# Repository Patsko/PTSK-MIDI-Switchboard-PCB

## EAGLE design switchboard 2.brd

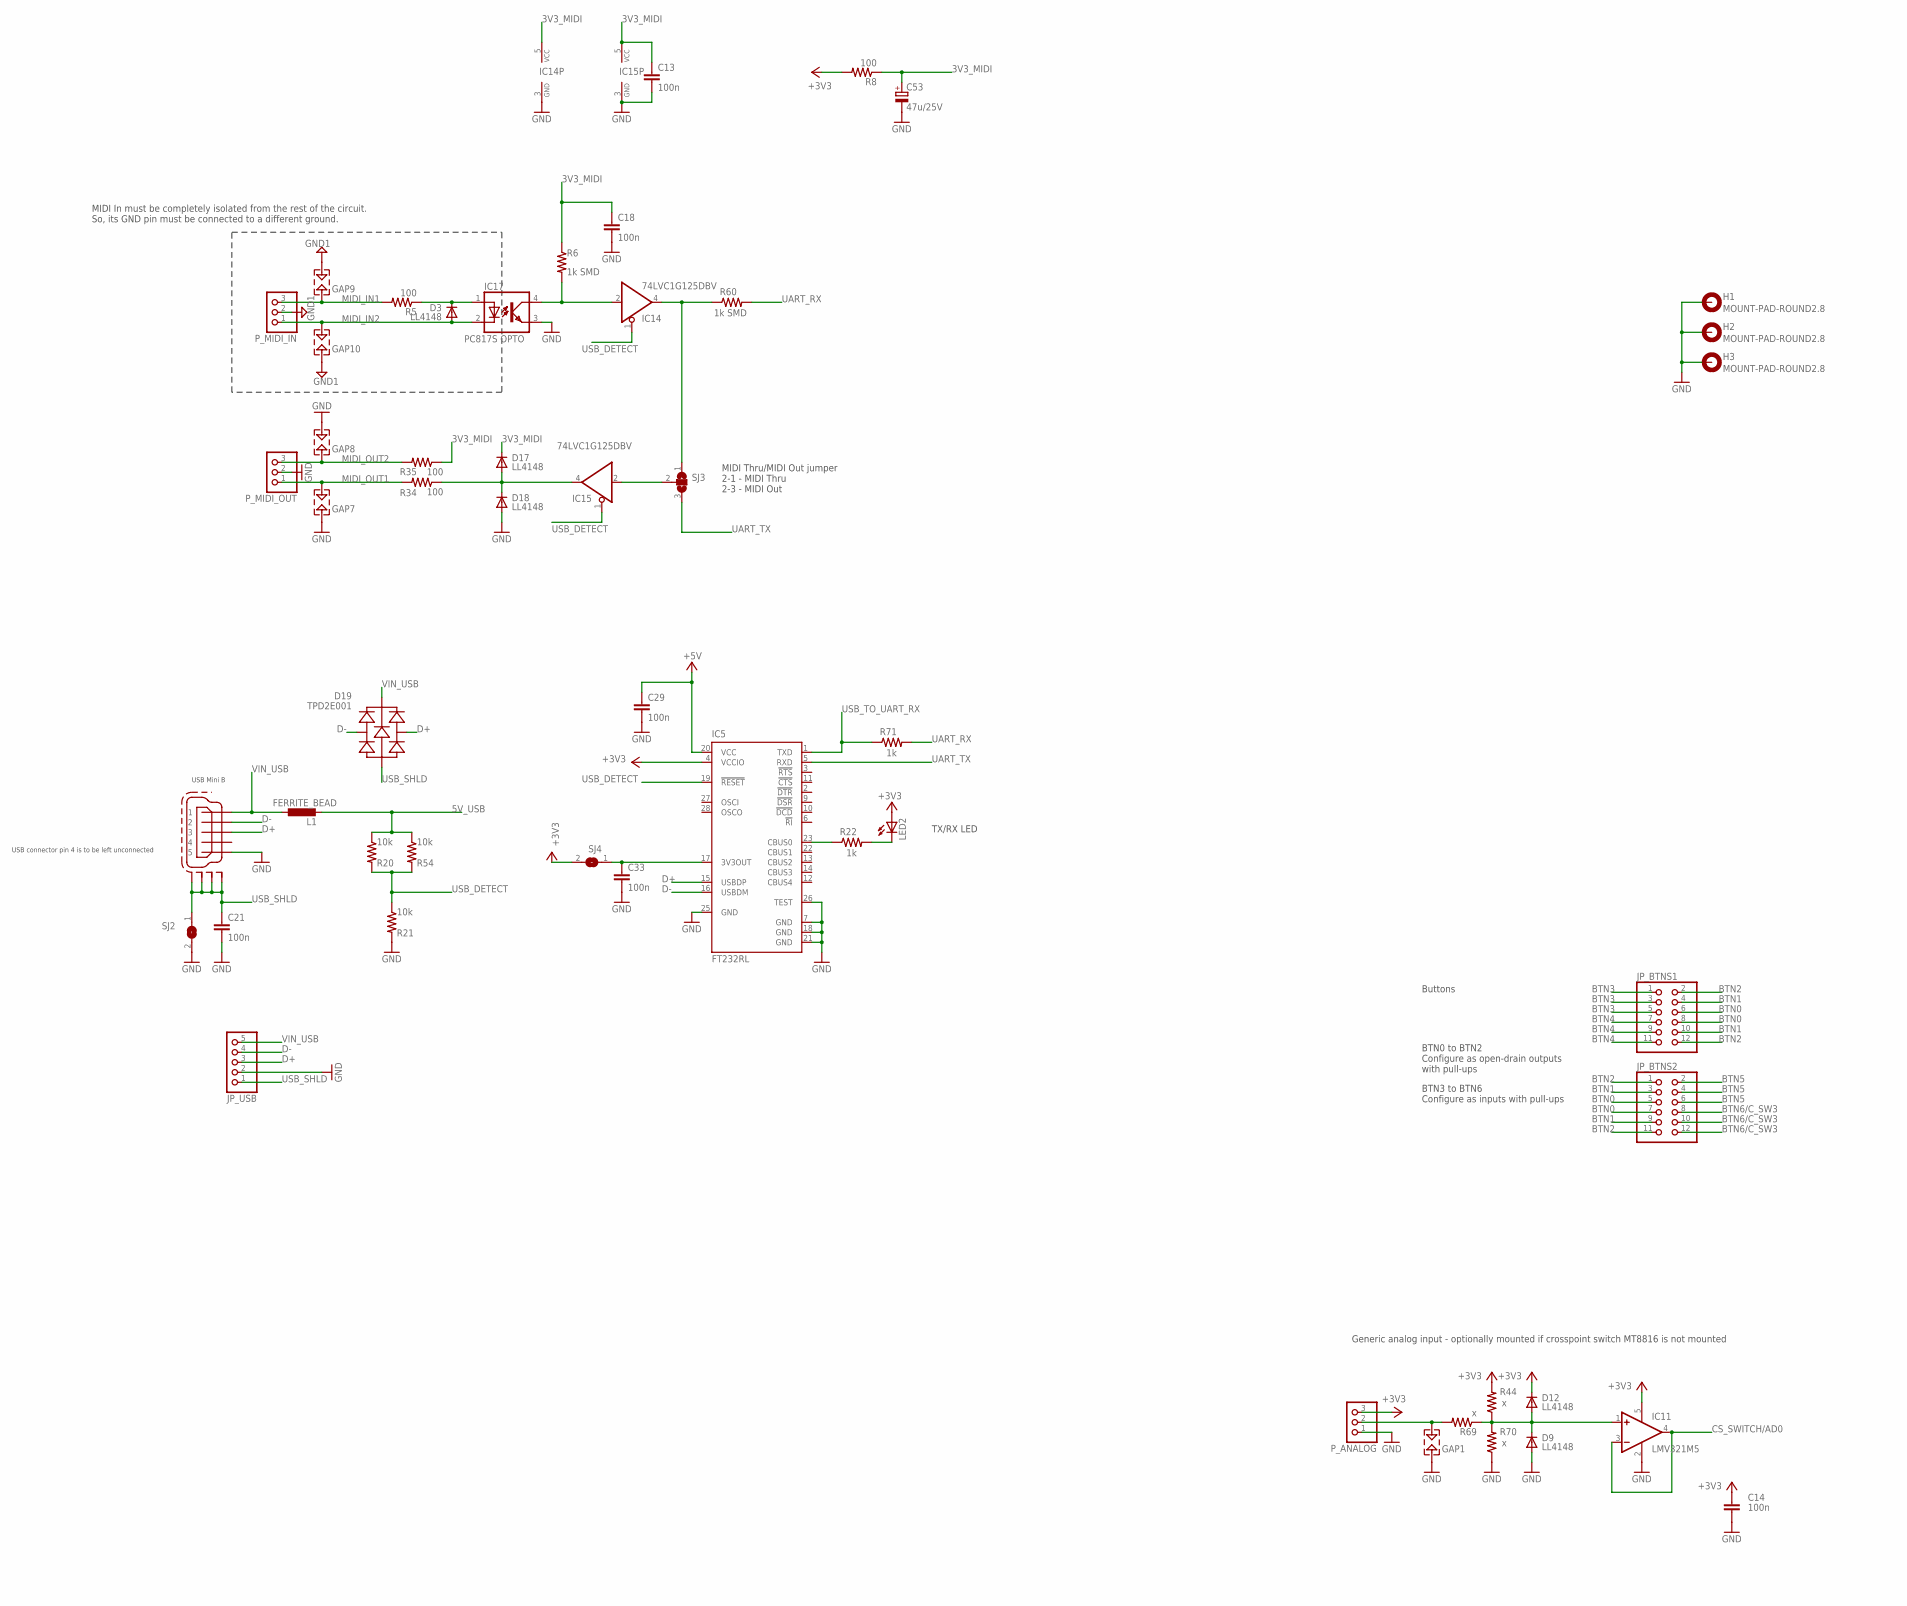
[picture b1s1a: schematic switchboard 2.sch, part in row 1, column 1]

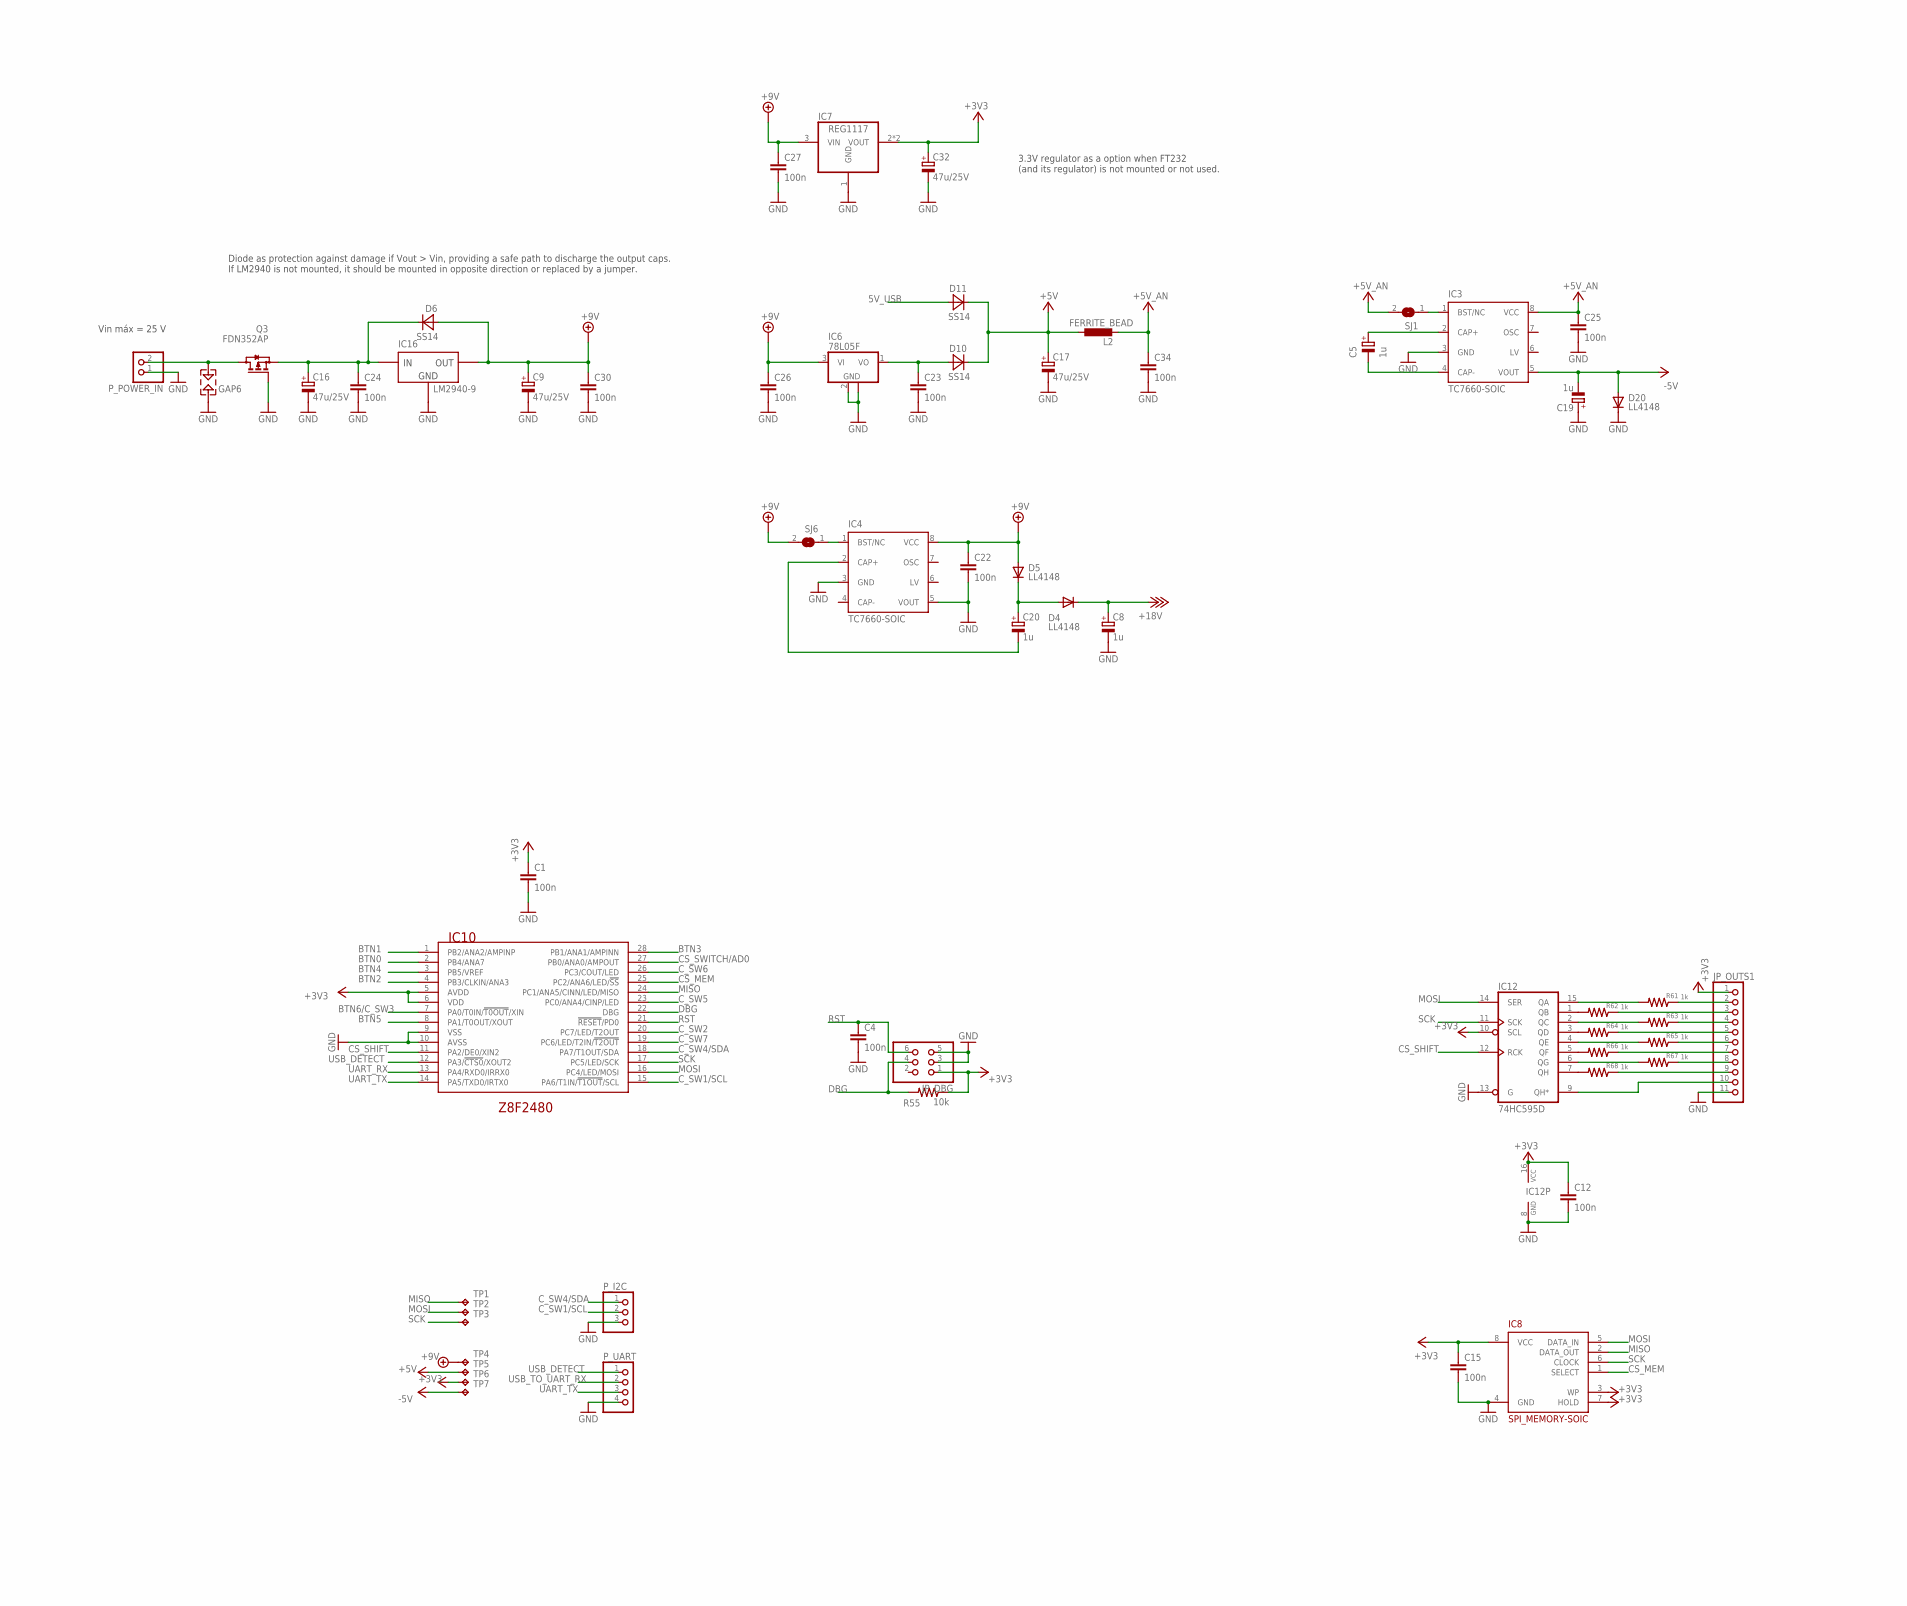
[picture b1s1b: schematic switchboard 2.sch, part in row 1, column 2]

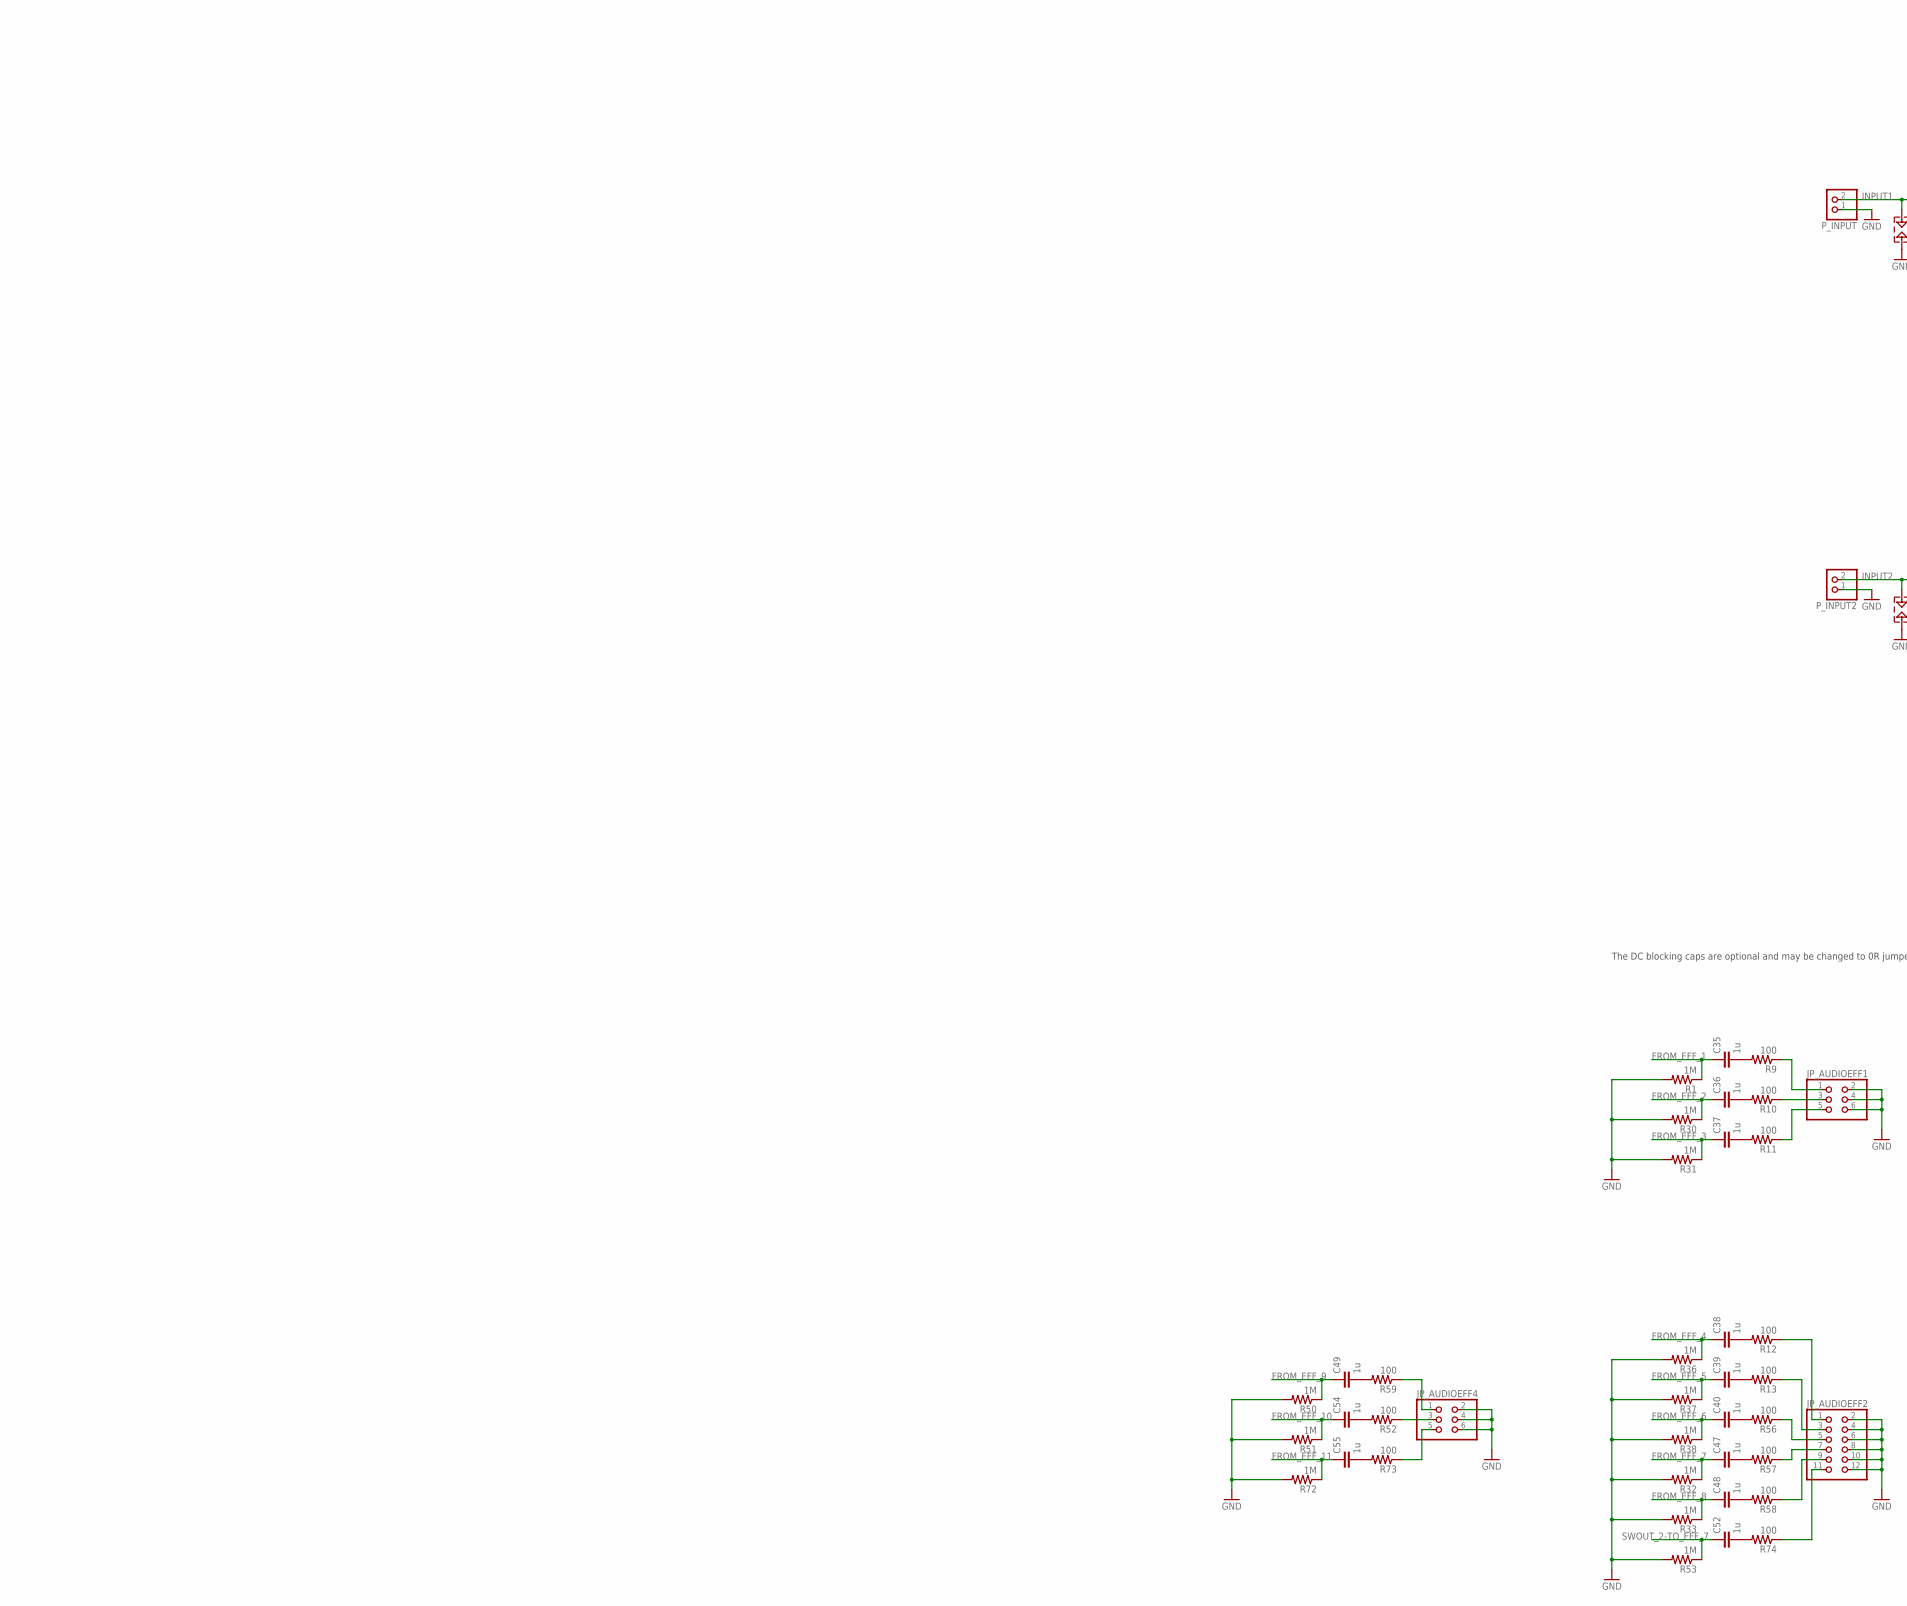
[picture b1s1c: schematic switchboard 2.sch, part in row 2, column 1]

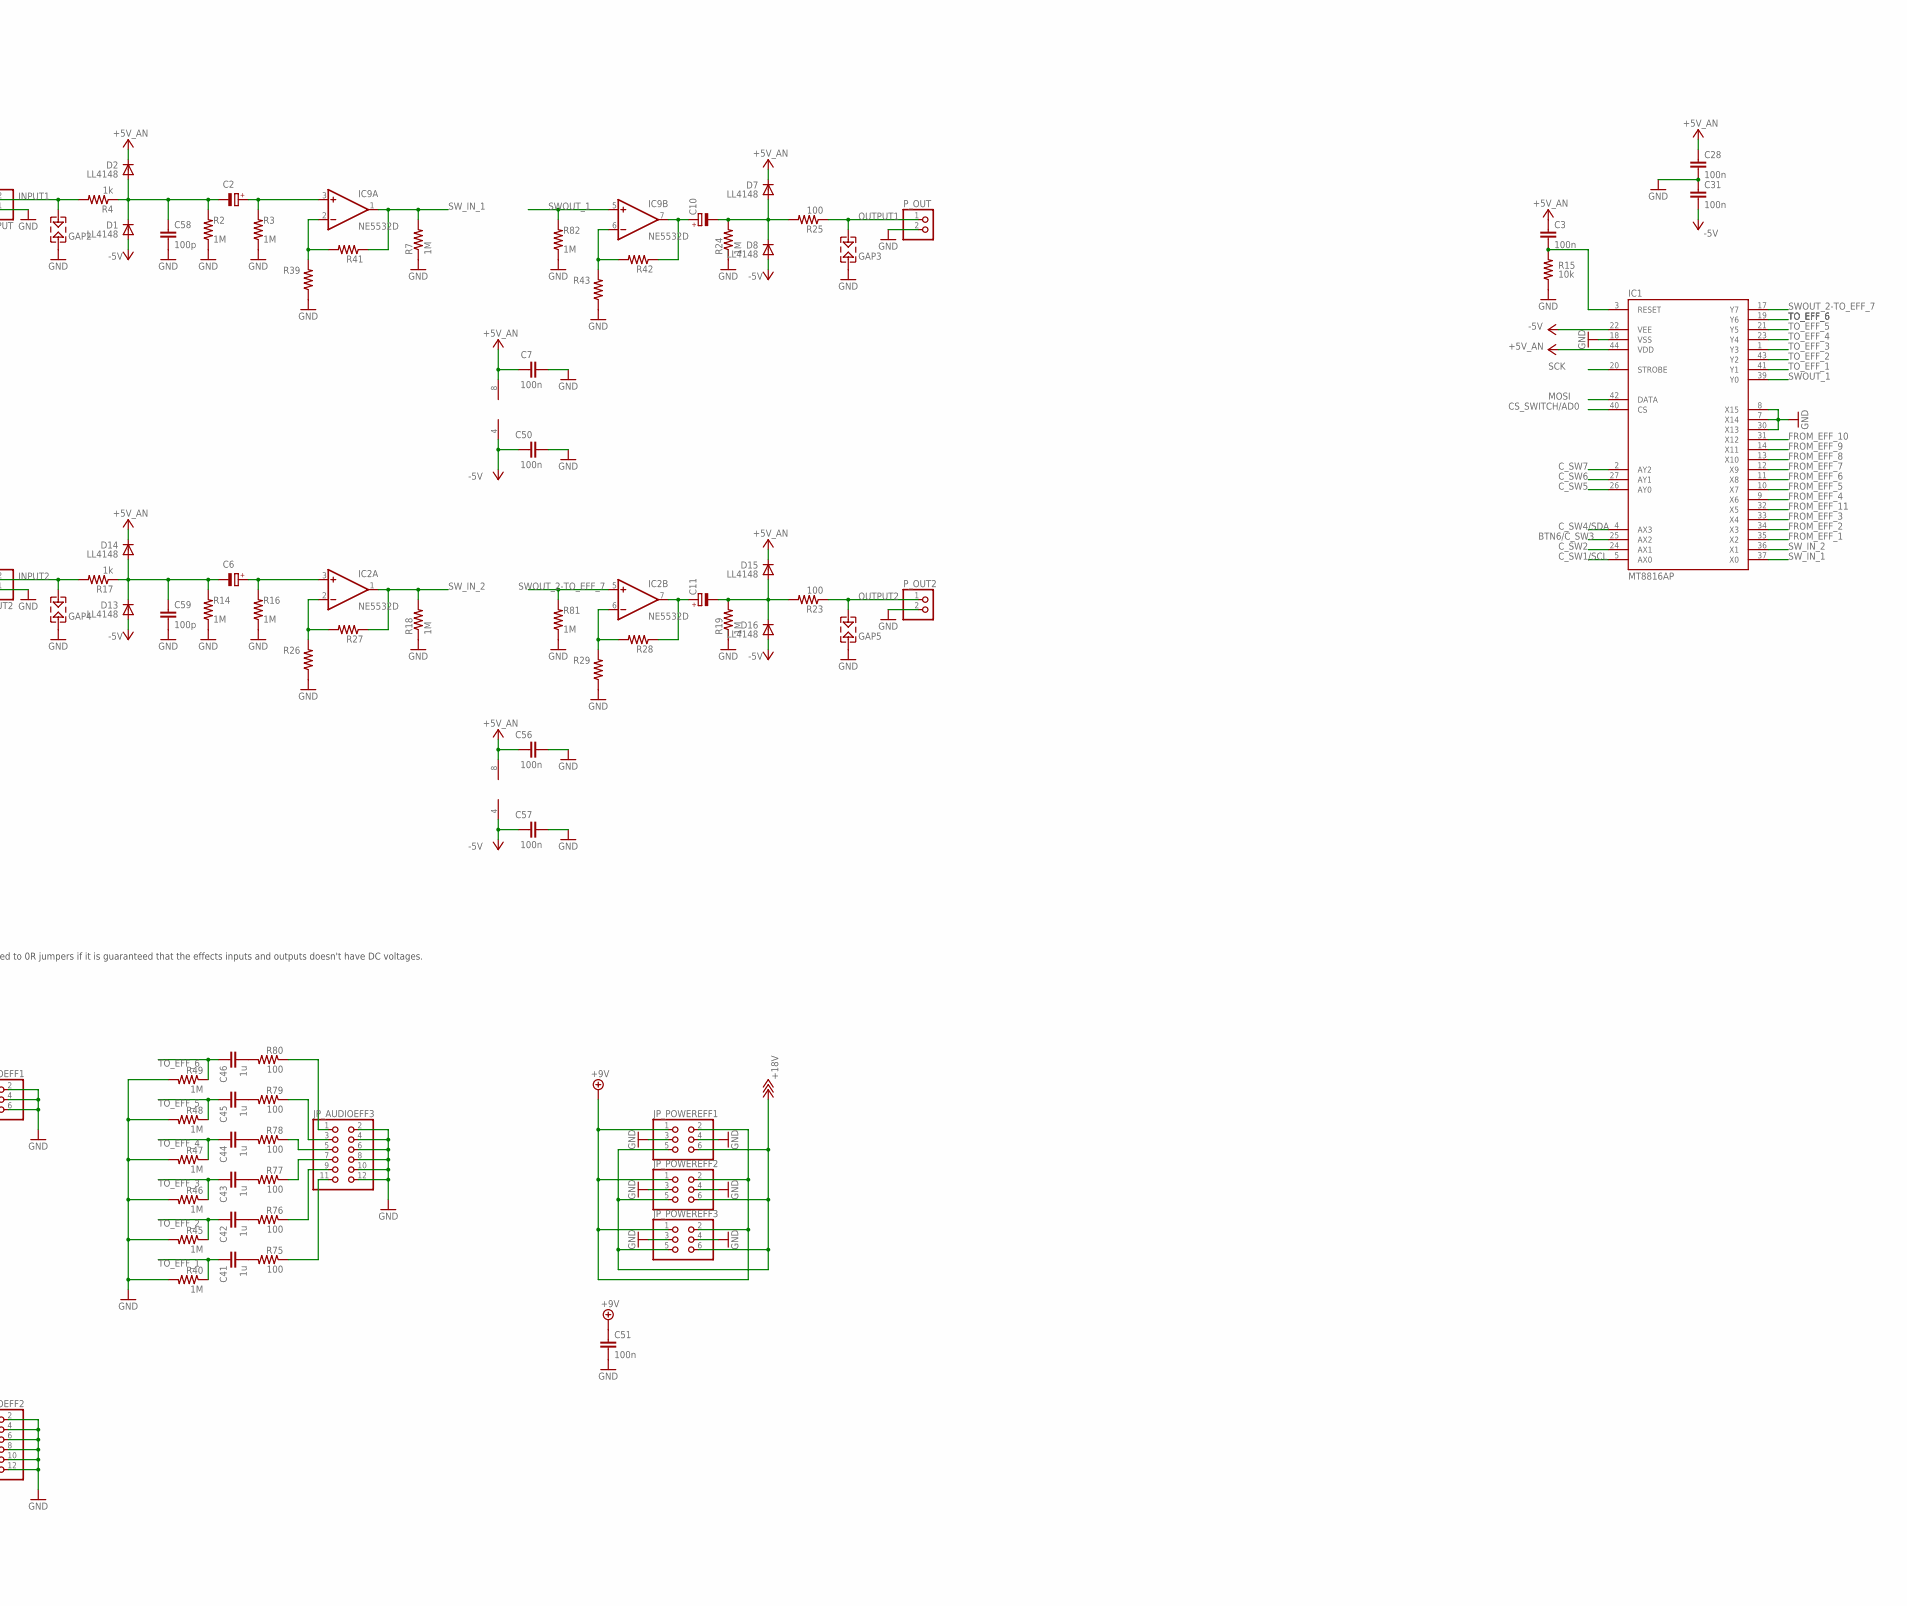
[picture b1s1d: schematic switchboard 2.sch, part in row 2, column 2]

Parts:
C1, C3, C4, C7, C12, C13, C14, C15, C18, C26, C28, C29, C30, C31, C33, C50, C51, C56, C57: 100n; C0603
C2, C6, C10, C11: CAP_POL; SMB-SMA-0805-0603
C5, C8, C19, C20: 1u; SMB-SMA-0805-0603
C9, C16, C17, C32, C53: 47u/25V; ALUMINUM-TANTALUM-CAP
C21, C22, C23, C24, C25, C27, C34: 100n; C0805
C35, C36, C37, C38, C39, C40, C41, C42, C43, C44, C45, C46, C47, C48, C49, C52, C54, C55: 1u; C0603
C58, C59: 100p; C0603
D1, D2, D3, D4, D5, D7, D8, D9, D12, D13, D14, D15, D16, D17, D18, D20: LL4148; MINIMELF
D6, D10, D11: SS14; SMA
D19: TPD2E001; SOT143B
GAP1, GAP2, GAP3, GAP4, GAP5, GAP6, GAP7, GAP8, GAP9, GAP10: SPARK_GAP; SPARK-GAP-8
H1, H2, H3: MOUNT-PAD-ROUND2.8; 2,8-PAD
IC1: MT8816AP; PLCC44
IC2, IC9: NE5532D; SO08
IC3, IC4: TC7660-SOIC; SOIC08
IC5: FT232RL; SSOP28
IC6: 78L05F; SOT89
IC7: REG1117; SOT223
IC8: SPI_MEMORY-SOIC; SOIC08
IC10: Z8F2480SO; SO28W
IC11: LMV321M5; SOT23-5
IC12: 74HC595D; SO16
IC14, IC15: 74LVC1G125DBV; SOT23-5
IC16: LM2940-9; SOT223
IC17: PC817S OPTO; DIL4-SMD
JP_AUDIOEFF1, JP_AUDIOEFF4: PINHD-2X03_2.54-SMD; 2X03SMD
JP_AUDIOEFF2, JP_AUDIOEFF3: PINHD-2X06_2.54-SMD; 2X06SMD
JP_BTNS1, JP_BTNS2: PINHD-2X06_2.54-SMD; 2X06SMD
JP_DBG: PINHD-2X3; 2X03
JP_OUTS1: PINHD-1X11; 1X11
JP_POWEREFF1, JP_POWEREFF2, JP_POWEREFF3: PINHD-2X03_2.54-SMD; 2X03SMD
JP_USB: PINHD-1X5; 1X05
L1, L2: FERRITE_BEAD; 0805
LED2: LEDCHIPLED_0805; CHIPLED_0805
P_ANALOG: PINHD-1X3; 1X03
P_I2C: PINHD-1X3; 1X03
P_INPUT, P_INPUT2: PINHD-1X2; 1X02
P_MIDI_IN: PINHD-1X3; 1X03
P_MIDI_OUT: PINHD-1X3; 1X03
P_OUT, P_OUT2: PINHD-1X2; 1X02
P_POWER_IN: PINHD-1X2; 1X02
P_UART: PINHD-1X4; 1X04
Q3: FDN352AP; SOT23
R1, R2, R3, R7, R14, R16, R18, R19, R24, R30, R31, R32, R33, R36, R37, R38, R40, R45, R46, R47, R48, R49, R50, R51, R53, R72, R81, R82: 1M; R0603
R4, R17, R22, R61, R62, R63, R64, R65, R66, R67, R68, R71: 1k; R0603
R5, R8, R9, R10, R11, R12, R13, R23, R25, R34, R35, R52, R56, R57, R58, R59, R73, R74, R75, R76, R77, R78, R79, R80: 100; R0603
R6, R60: 1k SMD; R0603
R15, R20, R21, R54, R55: 10k; R0603
R26, R27, R28, R29: 1M SMD; R0603
R39, R41, R42, R43: X; R0603
R44, R69, R70: x; R0603
SJ1, SJ2, SJ4, SJ6: SJ
SJ3: SJ2W; SJ_2
TP1, TP2, TP3, TP4, TP5, TP6, TP7: TPB1,27; B1,27
X1: MINI-USB-SCHIELD-32005-301; 32005-301

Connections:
3V3_MIDI: C13.1, C18.1, C53.+, D17.C, IC14.5 (VCC), IC15.5 (VCC), R6.1, R8.1, R35.1
5V_USB: D11.A, L1.2, R20.1, R54.1
+3V3: C1.1, C12.1, C14.1, C15.1, C32.+, D12.C, IC5.4 (VCCIO), IC7.2 (VOUT), IC7.TAB (VOUT), IC8.3 (WP), IC8.7 (HOLD), IC8.8 (VCC), IC10.5 (AVDD), IC10.6 (VDD), IC11.5 (V+), IC12.10 (SCL), IC12.16 (VCC), JP_DBG.1, JP_OUTS1.1, LED2.A, P_ANALOG.3, R8.2, R44.2, R55.1, SJ4.2, TP6.TP
+5V: C17.+, C29.1, D10.C, D11.C, IC5.20 (VCC), L2.1, TP5.TP
+5V_AN: C3.1, C7.1, C25.1, C28.1, C34.1, C56.1, D2.C, D7.C, D14.C, D15.C, IC1.44 (VDD), IC2.8 (V+), IC3.8 (VCC), IC9.8 (V+), L2.2, SJ1.2
+9V: C9.+, C22.1, C26.1, C27.1, C30.1, C51.1, D5.A, D6.A, IC4.8 (VCC), IC6.3 (VI), IC7.3 (VIN), IC16.3 (OUT), JP_POWEREFF1.1, JP_POWEREFF1.2, JP_POWEREFF2.1, JP_POWEREFF2.2, JP_POWEREFF3.1, JP_POWEREFF3.2, SJ6.2, TP4.TP
+18V: C8.+, D4.C, JP_POWEREFF1.5, JP_POWEREFF1.6, JP_POWEREFF2.5, JP_POWEREFF2.6, JP_POWEREFF3.5, JP_POWEREFF3.6
-5V: C19.-, C31.2, C50.1, C57.1, D1.A, D8.A, D13.A, D16.A, D20.A, IC1.22 (VEE), IC2.4 (V-), IC3.5 (VOUT), IC9.4 (V-), TP7.TP
AD0: D9.C, D12.A, IC11.1 (+IN), R44.1, R69.1, R70.2
BTN0: IC10.2 (PB4/ANA7), JP_BTNS1.6, JP_BTNS1.8, JP_BTNS2.5, JP_BTNS2.7
BTN1: IC10.1 (PB2/ANA2/AMPINP), JP_BTNS1.4, JP_BTNS1.10, JP_BTNS2.3, JP_BTNS2.9
BTN2: IC10.4 (PB3/CLKIN/ANA3), JP_BTNS1.2, JP_BTNS1.12, JP_BTNS2.1, JP_BTNS2.11
BTN3: IC10.28 (PB1/ANA1/AMPINN), JP_BTNS1.1, JP_BTNS1.3, JP_BTNS1.5
BTN4: IC10.3 (PB5/VREF), JP_BTNS1.7, JP_BTNS1.9, JP_BTNS1.11
BTN5: IC10.8 (PA1/T0OUT/XOUT), JP_BTNS2.2, JP_BTNS2.4, JP_BTNS2.6
BTN6/C_SW3: IC1.25 (AX2), IC10.7 (PA0/T0IN/!T0OUT!/XIN), JP_BTNS2.8, JP_BTNS2.10, JP_BTNS2.12
CS_MEM: IC8.1 (SELECT), IC10.25 (PC2/ANA6/LED/!SS)
CS_SHIFT: IC10.11 (PA2/DE0/XIN2), IC12.12 (RCK)
CS_SWITCH/AD0: IC1.40 (CS), IC10.27 (PB0/ANA0/AMPOUT), IC11.3 (-IN), IC11.4 (OUT)
C_SW1/SCL: IC1.5 (AX0), IC10.15 (PA6/T1IN/!T1OUT!/SCL), P_I2C.2
C_SW2: IC1.24 (AX1), IC10.20 (PC7/LED/T2OUT)
C_SW4/SDA: IC1.4 (AX3), IC10.18 (PA7/T1OUT/SDA), P_I2C.1
C_SW5: IC1.26 (AY0), IC10.23 (PC0/ANA4/CINP/LED)
C_SW6: IC1.27 (AY1), IC10.26 (PC3/COUT/LED)
C_SW7: IC1.2 (AY2), IC10.19 (PC6/LED/T2IN/!T2OUT!)
D+: D19.3 (IO2), IC5.15 (USBDP), JP_USB.3, X1.3
D-: D19.2 (IO1), IC5.16 (USBDM), JP_USB.4, X1.2
DBG: IC10.22 (DBG), JP_DBG.4, R55.2
FROM_EFF_1: C35.1, IC1.35 (X2), R1.1
FROM_EFF_2: C36.1, IC1.34 (X3), R30.1
FROM_EFF_3: C37.1, IC1.33 (X4), R31.1
FROM_EFF_4: C38.1, IC1.9 (X6), R36.1
FROM_EFF_5: C39.1, IC1.10 (X7), R37.1
FROM_EFF_6: C40.1, IC1.11 (X8), R38.1
FROM_EFF_7: C47.1, IC1.12 (X9), R32.1
FROM_EFF_8: C48.1, IC1.13 (X10), R33.1
FROM_EFF_9: C49.1, IC1.14 (X11), R50.1
FROM_EFF_10: C54.1, IC1.31 (X12), R51.1
FROM_EFF_11: C55.1, IC1.32 (X5), R72.1
GND: C1.2, C4.2, C7.2, C8.-, C9.-, C12.2, C13.2, C14.2, C15.2, C16.-, C17.-, C18.2, C19.+, C21.2, C22.2, C23.2, C24.2, C25.2, C26.2, C27.2, C28.2, C29.2, C30.2, C31.1, C32.-, C33.2, C34.2, C50.2, C51.2, C53.-, C56.2, C57.2, C58.2, C59.2, D9.A, D18.A, D20.C, GAP1.P$2 (2), GAP2.P$2 (2), GAP3.P$2 (2), GAP4.P$2 (2), GAP5.P$2 (2), GAP6.P$2 (2), GAP7.P$2 (2), GAP8.P$1 (1), H1.B2,8, H2.B2,8, H3.B2,8, IC1.7 (X14), IC1.8 (X15), IC1.18 (VSS), IC1.30 (X13), IC3.3 (GND), IC4.3 (GND), IC4.5 (VOUT), IC5.7 (GND), IC5.18 (GND), IC5.21 (GND), IC5.25 (GND), IC5.26 (TEST), IC6.2 (GND), IC6.2@1 (GND), IC7.1 (GND), IC8.4 (GND), IC10.9 (VSS), IC10.10 (AVSS), IC11.2 (V-), IC12.8 (GND), IC12.13 (G), IC14.3 (GND), IC15.3 (GND), IC16.2 (GND), IC16.TAB (GND), IC17.3 (EMIT), JP_AUDIOEFF1.2, JP_AUDIOEFF1.4, JP_AUDIOEFF1.6, JP_AUDIOEFF2.2, JP_AUDIOEFF2.4, JP_AUDIOEFF2.6, JP_AUDIOEFF2.8, JP_AUDIOEFF2.10, JP_AUDIOEFF2.12, JP_AUDIOEFF3.2, JP_AUDIOEFF3.4, JP_AUDIOEFF3.6, JP_AUDIOEFF3.8, JP_AUDIOEFF3.10, JP_AUDIOEFF3.12, JP_AUDIOEFF4.2, JP_AUDIOEFF4.4, JP_AUDIOEFF4.6, JP_DBG.3, JP_DBG.5, JP_OUTS1.11, JP_POWEREFF1.3, JP_POWEREFF1.4, JP_POWEREFF2.3, JP_POWEREFF2.4, JP_POWEREFF3.3, JP_POWEREFF3.4, JP_USB.2, P_ANALOG.1, P_I2C.3, P_INPUT.1, P_INPUT2.1, P_MIDI_OUT.2, P_OUT.2, P_OUT2.2, P_POWER_IN.1, P_UART.4, Q3.1 (G), R1.2, R2.1, R3.1, R7.1, R14.1, R15.1, R16.1, R18.1, R19.1, R21.2, R24.1, R26.1, R29.1, R30.2, R31.2, R32.2, R33.2, R36.2, R37.2, R38.2, R39.1, R40.2, R43.1, R45.2, R46.2, R47.2, R48.2, R49.2, R50.2, R51.2, R53.2, R70.1, R72.2, R81.1, R82.1, SJ2.2, X1.5
GND1: GAP9.P$1 (1), GAP10.P$2 (2), P_MIDI_IN.2
INPUT1: GAP2.P$1 (1), P_INPUT.2, R4.2
INPUT2: GAP4.P$1 (1), P_INPUT2.2, R17.2
MIDI_IN1: GAP9.P$2 (2), P_MIDI_IN.3, R5.2
MIDI_IN2: D3.A, GAP10.P$1 (1), IC17.2 (C), P_MIDI_IN.1
MIDI_OUT1: GAP7.P$1 (1), P_MIDI_OUT.1, R34.2
MIDI_OUT2: GAP8.P$2 (2), P_MIDI_OUT.3, R35.2
MISO: IC8.2 (DATA_OUT), IC10.24 (PC1/ANA5/CINN/LED/MISO), TP1.TP
MOSI: IC1.42 (DATA), IC8.5 (DATA_IN), IC10.16 (PC4/LED/MOSI), IC12.14 (SER), TP2.TP
unnamed: IC9.2 (-IN), R39.2, R41.2
unnamed: D17.A, D18.C, IC15.4 (O), R34.1
unnamed: C2.+, IC9.3 (+IN), R3.2
unnamed: C2.-, C58.1, D1.C, D2.A, R2.2, R4.1
unnamed: IC3.1 (BST/NC), SJ1.1
unnamed: IC4.1 (BST/NC), SJ6.1
unnamed: IC9.6 (-IN), R42.2, R43.2
unnamed: C10.+, IC9.7 (OUT), R42.1
unnamed: JP_AUDIOEFF2.1, R12.1
unnamed: C20.+, D4.A, D5.C
unnamed: JP_AUDIOEFF1.1, R9.1
unnamed: C23.1, D10.A, IC6.1 (VO)
unnamed: C10.-, D7.A, D8.C, R24.2, R25.2
unnamed: C35.2, R9.2
unnamed: C36.2, R10.2
unnamed: C37.2, R11.2
unnamed: C38.2, R12.2
unnamed: C54.2, R52.2
unnamed: IC12.15 (QA), R61.2
unnamed: JP_AUDIOEFF3.11, R75.1
unnamed: IC12.1 (QB), R62.2
unnamed: IC12.2 (QC), R63.2
unnamed: IC12.3 (QD), R64.2
unnamed: C16.+, C24.1, D6.C, IC16.1 (IN), Q3.2 (S)
unnamed: IC12.4 (QE), R65.2
unnamed: C6.+, IC2.3 (+IN), R16.2
unnamed: D3.C, IC17.1 (A), R5.1
unnamed: IC12.5 (QF), R66.2
unnamed: IC12.6 (QG), R67.2
unnamed: IC12.7 (QH), R68.2
unnamed: JP_AUDIOEFF3.9, R76.1
unnamed: LED2.C, R22.2
unnamed: GAP1.P$1 (1), P_ANALOG.2, R69.2
unnamed: C33.1, IC5.17 (3V3OUT), SJ4.1
unnamed: JP_OUTS1.2, R61.1
unnamed: JP_OUTS1.3, R62.1
unnamed: JP_OUTS1.4, R63.1
unnamed: JP_OUTS1.5, R64.1
unnamed: JP_OUTS1.6, R65.1
unnamed: JP_OUTS1.7, R66.1
unnamed: JP_OUTS1.8, R67.1
unnamed: JP_OUTS1.9, R68.1
unnamed: IC12.9 (QH*), JP_OUTS1.10
unnamed: IC5.23 (CBUS0), R22.1
unnamed: C5.+, IC3.2 (CAP+)
unnamed: C5.-, IC3.4 (CAP-)
unnamed: GAP6.P$1 (1), P_POWER_IN.2, Q3.3 (D)
unnamed: C39.2, R13.2
unnamed: C40.2, R56.2
unnamed: C47.2, R57.2
unnamed: JP_AUDIOEFF3.7, R77.1
unnamed: JP_AUDIOEFF3.5, R78.1
unnamed: C6.-, C59.1, D13.C, D14.A, R14.2, R17.1
unnamed: C11.+, IC2.7 (OUT), R28.1
unnamed: C11.-, D15.A, D16.C, R19.2, R23.2
unnamed: IC2.2 (-IN), R26.2, R27.2
unnamed: IC2.6 (-IN), R28.2, R29.2
unnamed: JP_AUDIOEFF3.3, R79.1
unnamed: C20.-, IC4.2 (CAP+)
unnamed: IC15.2 (I), SJ3.2
unnamed: JP_AUDIOEFF3.1, R80.1
unnamed: C48.2, R58.2
unnamed: C55.2, R73.2
unnamed: C49.2, R59.2
unnamed: JP_AUDIOEFF2.11, R74.1
unnamed: JP_AUDIOEFF4.5, R73.1
unnamed: C52.2, R74.2
unnamed: JP_AUDIOEFF1.3, R10.1
unnamed: JP_AUDIOEFF4.3, R52.1
unnamed: JP_AUDIOEFF4.1, R59.1
unnamed: JP_AUDIOEFF1.5, R11.1
unnamed: JP_AUDIOEFF2.3, R13.1
unnamed: JP_AUDIOEFF2.9, R58.1
unnamed: JP_AUDIOEFF2.5, R56.1
unnamed: JP_AUDIOEFF2.7, R57.1
unnamed: C43.2, R77.2
unnamed: C41.2, R75.2
unnamed: C42.2, R76.2
unnamed: C44.2, R78.2
unnamed: C45.2, R79.2
unnamed: C46.2, R80.2
unnamed: IC14.4 (O), R60.1, SJ3.1
unnamed: C3.2, IC1.3 (RESET), R15.2
unnamed: IC14.2 (I), IC17.4 (COL), R6.2
OUTPUT1: GAP3.P$1 (1), P_OUT.1, R25.1
OUTPUT2: GAP5.P$1 (1), P_OUT2.1, R23.1
RST: C4.1, IC10.21 (!RESET!/PD0), JP_DBG.6
SCK: IC1.20 (STROBE), IC8.6 (CLOCK), IC10.17 (PC5/LED/SCK), IC12.11 (SCK), TP3.TP
SWOUT_1: IC1.39 (Y0), IC9.5 (+IN), R82.2
SWOUT_2-TO_EFF_7: C52.1, IC1.17 (Y7), IC2.5 (+IN), R53.1, R81.2
SW_IN_1: IC1.37 (X0), IC9.1 (OUT), R7.2, R41.1
SW_IN_2: IC1.36 (X1), IC2.1 (OUT), R18.2, R27.1
TO_EFF_1: C41.1, IC1.41 (Y1), R40.1
TO_EFF_2: C42.1, IC1.43 (Y2), R45.1
TO_EFF_3: C43.1, IC1.1 (Y3), R46.1
TO_EFF_4: C44.1, IC1.23 (Y4), R47.1
TO_EFF_5: C45.1, IC1.21 (Y5), R48.1
TO_EFF_6: C46.1, IC1.19 (Y6), R49.1
UART_RX: IC10.13 (PA4/RXD0/IRRX0), R60.2, R71.2
UART_TX: IC5.5 (RXD), IC10.14 (PA5/TXD0/IRTX0), P_UART.3, SJ3.3
USB_DETECT: IC5.19 (!RESET), IC10.12 (PA3/!CTS0!/XOUT2), IC14.1 (OE), IC15.1 (OE), P_UART.1, R20.2, R21.1, R54.2
USB_SHLD: C21.1, D19.1 (GND), JP_USB.1, SJ2.1, X1.M1 (S1), X1.M2 (S2), X1.M3 (S3), X1.M4 (S4)
USB_TO_UART_RX: IC5.1 (TXD), P_UART.2, R71.1
VIN_USB: D19.4 (VCC), JP_USB.5, L1.1, X1.1

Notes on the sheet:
BTN0 to BTN2 Configure as open-drain outputs with pull-ups
BTN3 to BTN6 Configure as inputs with pull-ups
3.3V regulator as a option when FT232 (and its regulator) is not mounted or not used.
USB connector pin 4 is to be left unconnected
USB Mini B
Generic analog input - optionally mounted if crosspoint switch MT8816 is not mounted
MIDI Thru/MIDI Out jumper 2-1 - MIDI Thru 2-3 - MIDI Out
The DC blocking caps are optional and may be changed to 0R jumpers if it is guaranteed that the effects inputs and outputs doesn't have DC voltages.
TX/RX LED
Buttons
Diode as protection against damage if Vout > Vin, providing a safe path to discharge the output caps. If LM2940 is not mounted, it should be mounted in opposite direction or replaced by a jumper.
MIDI In must be completely isolated from the rest of the circuit. So, its GND pin must be connected to a different ground.
Vin máx = 25 V

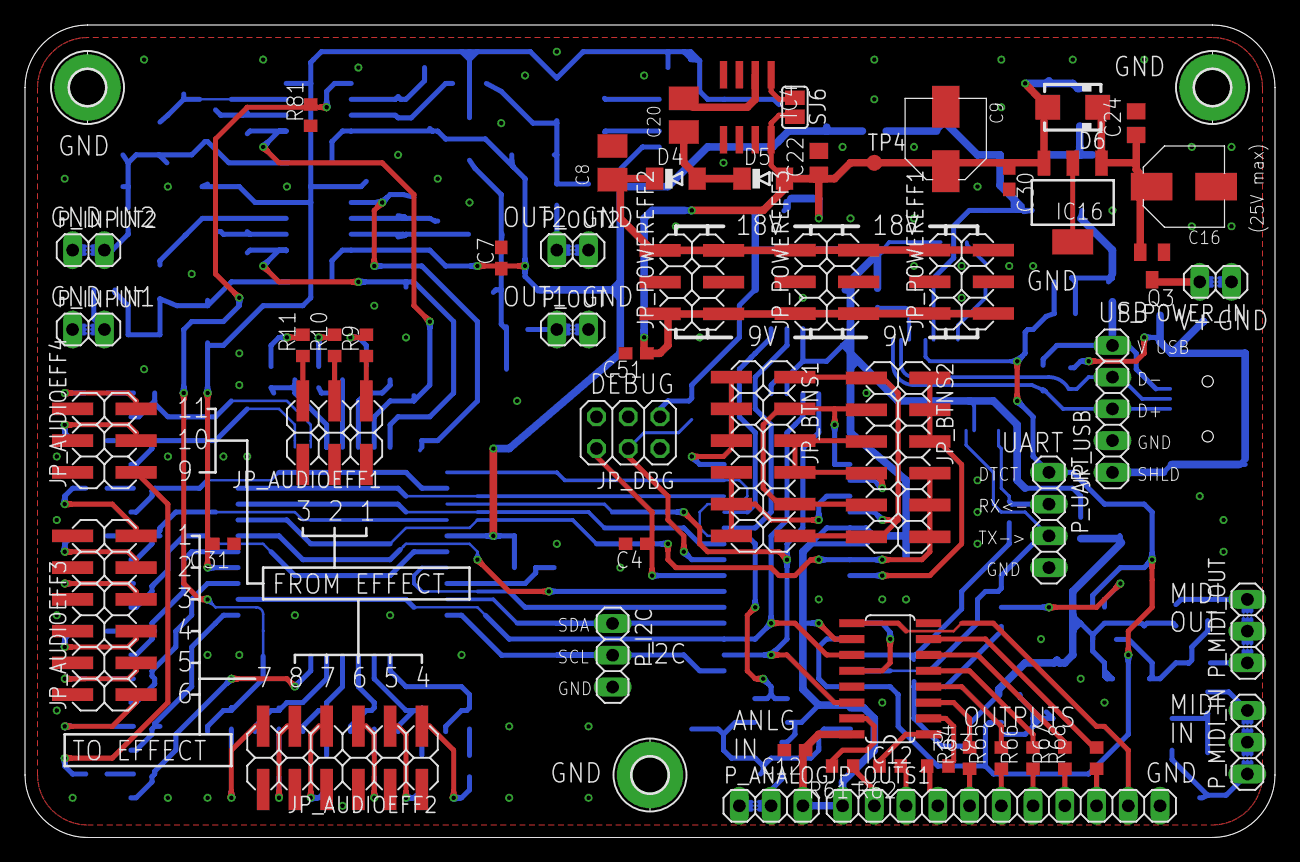
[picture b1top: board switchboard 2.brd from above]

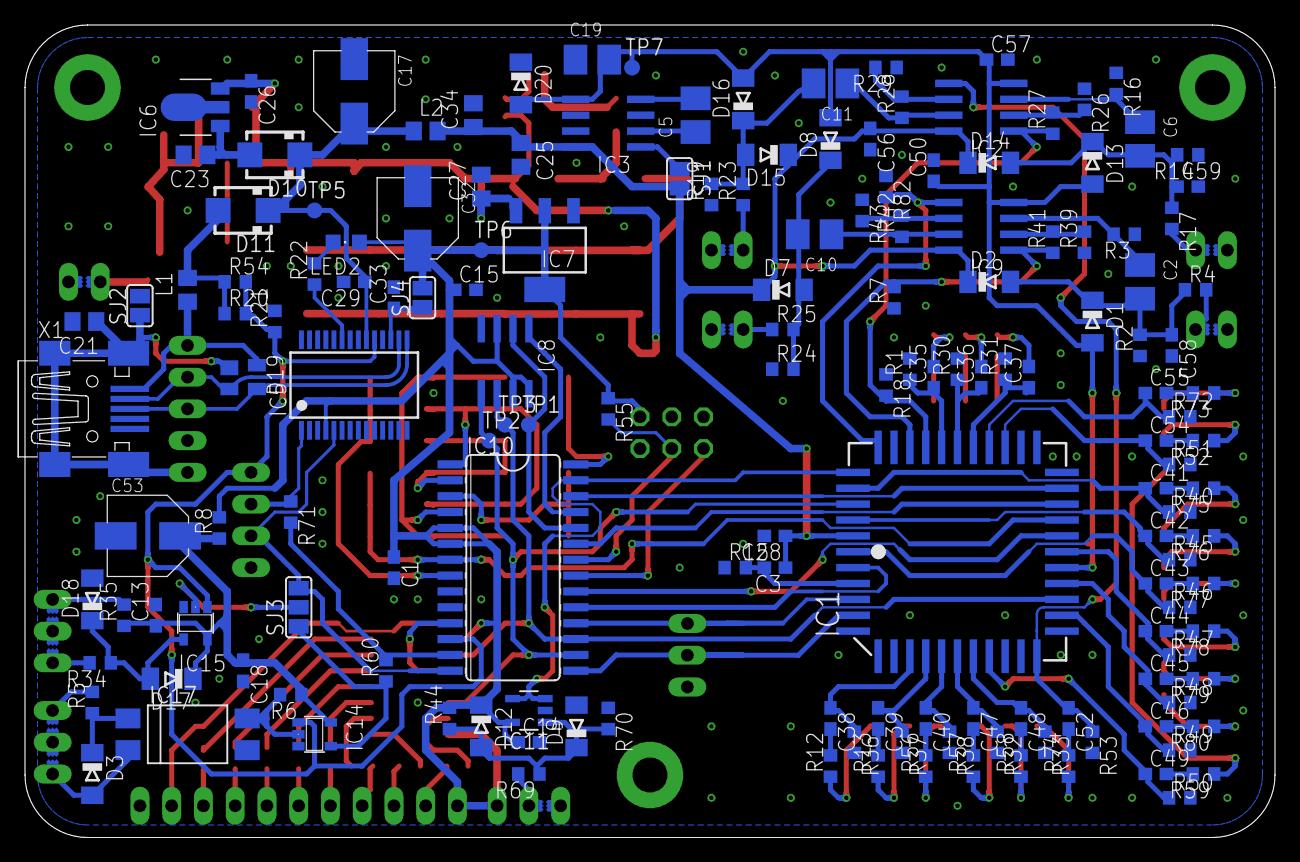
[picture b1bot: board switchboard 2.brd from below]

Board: 2 copper layers, 100.0 x 65.0 mm, 229 parts (171 on the bottom side), 153 nets.

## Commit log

2015-12-21 Commit inicial
2015-12-22 Desenvolvimento do esquematico.
2015-12-26 Conclusao geral do esquematico e inicio do desenvolvimento da placa.
2015-12-29 Desenvolvimento do esquematico e placa
2015-12-29 Alteracoes no projeto - remocao de dois efeitos do switchboard e seus componentes associados para chaveamento.
2016-09-03 Alteraoes no layout
2016-09-18 Desenvolvimento do esquematico: adicao de regulador ua78L05, alteracoes nos pinos do MCU, etc.
2016-09-29 Desenvolvimento do esquematico: alteracao para uso de regulador zener para 3.3V, alteracoes no optoacoplador e circuito MIDI, etc.
2016-12-03 Switch arrangement changed from 4053 to crosspoint switch.
2016-12-04 Addition of MIDI Thru mounting option. Routing of crosspoint switch input and output signals.
2016-12-08 Ajustes na alimentacao: troca de regulador zener por CJ1117, adicao de diodos OR para 5V, adicao de jumper de selecao para 3.3V, adicao de filtro para 5V analogico. Adicao de pinos para acesso aos si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
2016-12-10 Input/output pinheaders and components added. Initial layout adjustments.
2017-02-15 MCU Z8F082 dropped. Bidirectional MOSFET level shifter added. Reset signal added on debug connector.
2017-04-21 General revisions and mods to the schematic - series resistors added to UART_RX, 3.3V selection jumper removed, USB_DETECT zener removed. Spark gaps added at audio inputs and outputs.
2017-05-28 Polarity protection changed from series diode to PMOS. Pinheaders addded to access the MCU pins directly. V+ and Vcc power supply symbols changed to +9V and +5V_AN, respectively. Spark gaps added.
2017-07-04 Signal names changed to clarify the direction to and from external effects.
2017-07-17 Pull-ups on crosspoint address lines and voltage translator on SCK/MOSI removed.
2017-12-03 Changes made after Eagle update.
2018-01-09 Thru-hole pinheaders changed to SMD pinheaders.
2018-01-09 RC filter added to MIDI 3V3 supply. GND1 added to connect the MIDI In cable shield.
2018-01-18 Series resistors added to all audio effects inputs and outputs. Overvoltage protection added to audio and MIDI outputs. ESD protection added to MIDI inputs and outputs. USB_DETECT signal added to UAR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
2018-01-23 ESD protection with TPD2E001 added to USB inputs.
2018-01-27 Layout development. Minor component name and package changes.
2018-02-01 Layout development.
2018-02-05 Layout development. Board dimensions changed.
2018-02-17 Layout development. Schematic changes to ease routing process. Some component package changes (mainly from 0805 to 0603).
2018-02-23 Layout development and schematic changes to ease routing process.
2018-03-03 Layout development. Ground planes added to top and bottom layers.
2018-03-10 Polarity inversion protection diode added to -5V. USB ESD protection connection changed from GND to USB shield. Layout development and changes to improve performance, considering current loops.
2018-03-12 Final adjustments to the schematic and layout. Cap added close to the generic input opamp. RC filter against EMI added to the audio inputs. Bias resistors added to output opamps.
2018-03-17 Final adjustments. Test points added to SPI and supplies. PTSK Engineering text added (in solder mask stop layer).
2018-03-29 Layout changes to improve manufacturability and EMC. RESET pin removed.
2018-03-29 Teardrops added to vias.
2018-03-31 Final adjustments. PLCC-44 and aluminum electrolytic cap packages updated.
2018-03-31 Final adjustments. Signal identification added on silkscreen.
2018-03-31 Final changes before manufacture: spark gaps changed from top to bottom layer, silkscreen changes due to differences between what Eagle displays and the gerber files generated, SMD pinheader packages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
2018-11-20 PCB version 1 fixes
    - Crosspoint switch MT8816 reset pin is active high. Resistor and capacitor positions on schematic and layout switched accordingly.
    - Audio out 1 and 2 silkscreen position corrected.
    - Resistors values on IC9 feedback paths changed from 1 M to undefined (to be defined if needed).
